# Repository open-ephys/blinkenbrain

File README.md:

# Blinkenbrain
A mouse brain pendant with chaotic tendencies. It implements a variant of the circuit described in

```
Simple Two-Transistor Single-Supply Resistor–Capacitor Chaotic Oscillator
Lars Keuninckx, Guy Van der Sande, and Jan Danckaert
IEEE TRANSACTIONS ON CIRCUITS AND SYSTEMS—II: EXPRESS BRIEFS, VOL. 62, NO. 9, SEPTEMBER 2015
```

and uses its strange dynamics to blink a blinkenlight.

## How does it blink?

The circuit consists of a RC phase shift oscillator (blue) combined with what amounts to a tunable Schmitt trigger (red).
The position of the trimpot (RV1) determines if the effect of the Schmitt trigger on the oscillator.

- When the wiper of RV1 is tuned to 0Ω, Q1B does not conduct, and the Schmitt trigger is effectively removed from the circuit
- When the wiper of RV1 is tuned to 100kΩ, Q1B acts as trigger without hysteresis, and therefore conducts in synchrony with the
  RC oscillator.
- When the wiper of RV1 is turned in between these two extremes, a hysteretic path is formed between Q1B's conducting and non-conducting states,
  which results in the emergence of two interacting unstable equilibria and, for some values of RV1, chaotic dynamics.

The gate of an N-channel MOSFET is tied to the collector of Q1A to drive the LED without influencing the
circuit's dynamics. The following image shows V<sub>TP4</sub> vs.V<sub>TP3</sub> when RV1 is tuned to ~70kΩ.

## License
"No Rights Reserved", CC0

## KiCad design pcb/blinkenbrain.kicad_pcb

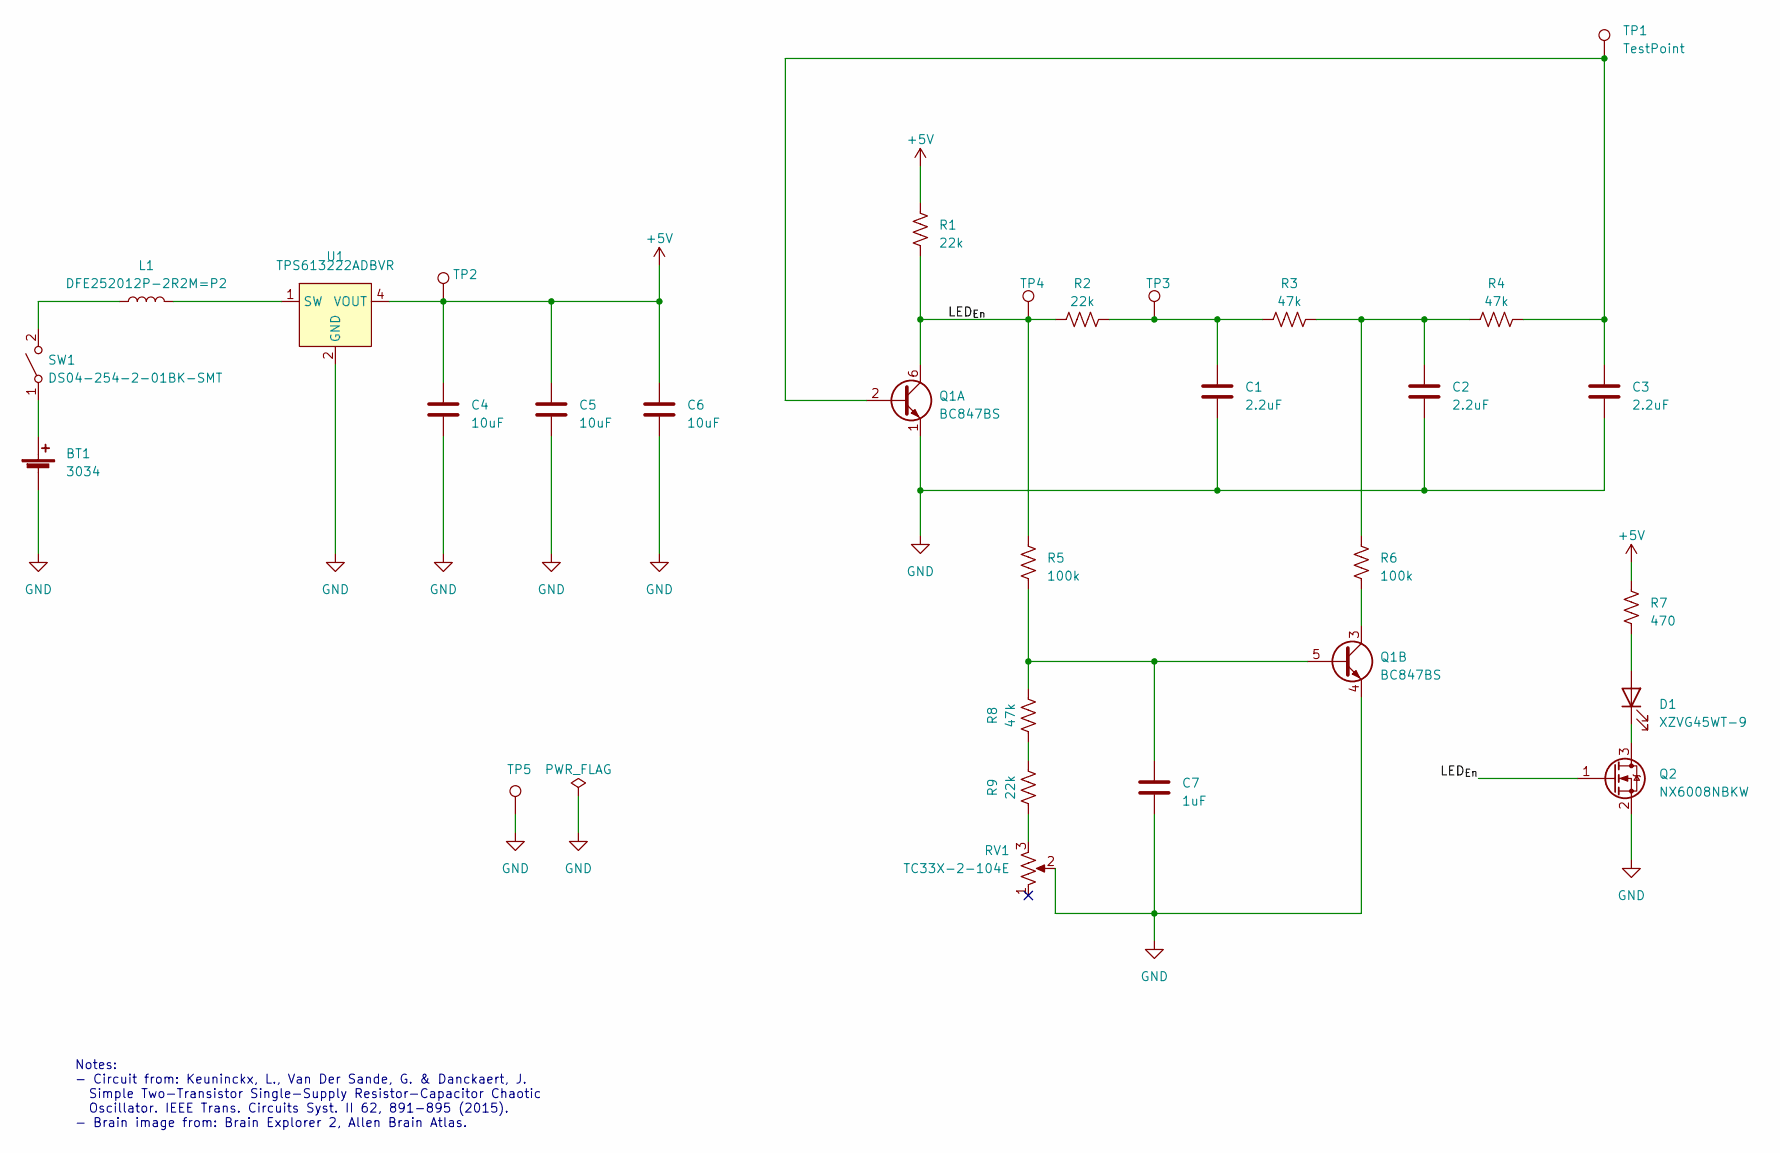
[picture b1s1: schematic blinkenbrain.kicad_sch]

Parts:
BT1: 3034; BatteryHolder_Keystone_3034_1x20mm
C1, C2, C3: 2.2uF; C_0603_1608Metric; Tolerance 5%; Voltage 10V
C4, C5, C6: 10uF; C_0603_1608Metric; Tolerance 20%; Voltage 16V
C7: 1uF; C_0603_1608Metric; Tolerance 5%; Voltage 10V
D1: XZVG45WT-9; SUNLED_PLCC2-INV
L1: DFE252012P-2R2M=P2; L_1008_2520Metric
Q1: BC847BS; SOT-363_SC-70-6
Q2: NX6008NBKW; SOT-23-3
R1, R2, R9: 22k; R_0402_1005Metric; Tolerance 1%
R3, R4, R8: 47k; R_0402_1005Metric; Tolerance 1%
R5, R6: 100k; R_0402_1005Metric; Tolerance 1%
R7: 470; R_0603_1608Metric; Tolerance 1%
RV1: TC33X-2-104E; BOURNS_TC33
SW1: DS04-254-2-01BK-SMT; SW_DIP_SPSTx01_Slide_6.7x4.1mm_W8.61mm_P2.54mm_LowProfile
TP1, TP2, TP3, TP4, TP5: TestPoint; TestPoint_Pad_D2.0mm
U1: TPS613222ADBVR; SOT-23-5

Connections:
+5V: C4.1, C5.1, C6.1, R1.1, R7.2, TP2.1, U1.4 (VOUT)
/LED_{En}: Q1.6 (C1), Q2.1 (G), R1.2, R2.1, R5.2, TP4.1
GND: BT1.2 (-), C1.2, C2.2, C3.2, C4.2, C5.2, C6.2, C7.2, Q1.1 (E1), Q1.4 (E2), Q2.2 (S), RV1.2, TP5.1, U1.2 (GND)
unnamed: BT1.1 (+), SW1.1 (A)
unnamed: C1.1, R2.2, R3.1, TP3.1
unnamed: C2.1, R3.2, R4.1, R6.2
unnamed: D1.2 (A), R7.1
unnamed: D1.1 (K), Q2.3 (D)
unnamed: C3.1, Q1.2 (B1), R4.2, TP1.1
unnamed: C7.1, Q1.5 (B2), R5.1, R8.2
unnamed: Q1.3 (C2), R6.1
unnamed: R8.1, R9.2
unnamed: R9.1, RV1.3
unnamed: L1.1, SW1.2 (B)
unnamed: L1.2, U1.1 (SW)

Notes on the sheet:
Notes: - Circuit from: Keuninckx, L., Van Der Sande, G. & Danckaert, J. Simple Two-Transistor Single-Supply Resistor-Capacitor Chaotic Oscillator. IEEE Trans. Circuits Syst. II 62, 891-895 (2015). - Brain image from: Brain Explorer 2, Allen Brain Atlas.

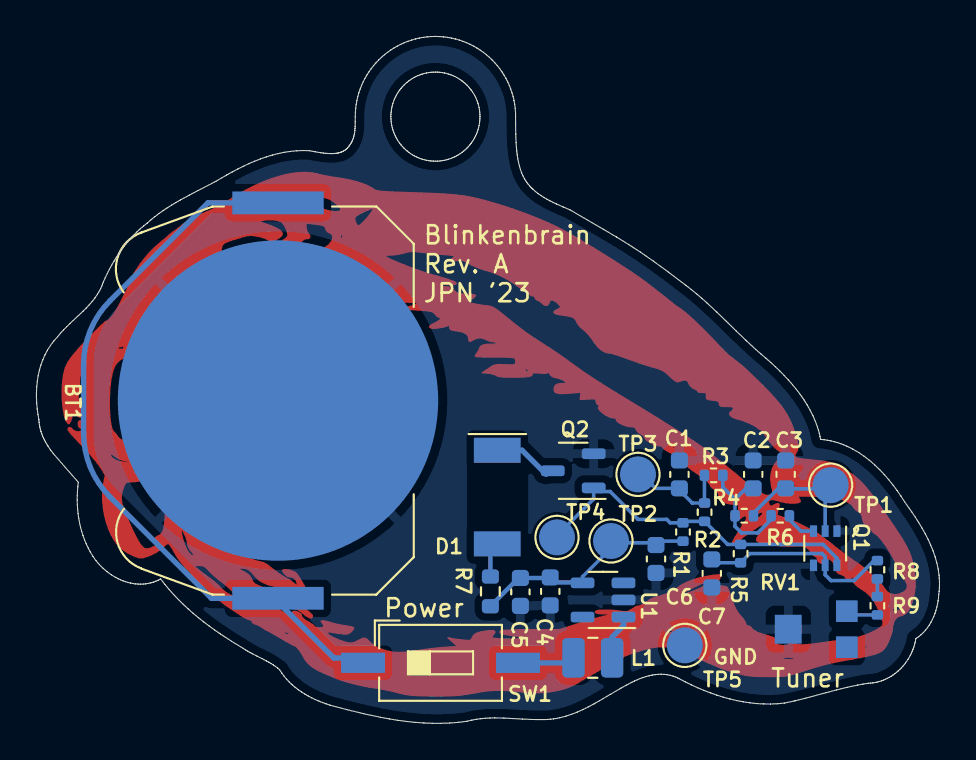
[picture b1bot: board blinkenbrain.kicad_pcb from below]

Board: 2 copper layers, 50.2 x 38.2 mm, 29 parts (29 on the bottom side), 15 nets.

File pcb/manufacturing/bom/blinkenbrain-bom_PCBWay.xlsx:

|  |  | Blinkenbrain 1 PCS BOM
Item # | *Designator | *Qty | Manufacturer | *Mfg Part # | Description / Value | *Package/Footprint | Type | Your Instructions / Notes
1 | U1 | 1 | Texas Instruments | TPS613222ADBVR | IC REG BOOST 5V 2.5A SOT23-5 | SOT23-5 | SMD
2 | SW1 | 1 | Dealon | SC-01KP | DIP switch, 1-bit | 0.1" DIP | SMD
3 | RV1 | 1 | Bourns | TC33X-2-104E | TRIMMER 100K OHM 0.1W J LEAD TOP | TC33 | SMD
4 | R1, R2, R9 | 3 | Walsin | WR04X2202FTL | RES 22K OHM 1/16W 1% 0402 SMD | 0402 | SMD
5 | R3, R4, R8 | 3 | YAGEO | RC0402FR-1347KL | RES 47K OHM 1/16W 1% 0402 SMD | 0402 | SMD
6 | R5, R6 | 2 | Walsin | WR04X1003FTL | RES 100K OHM 1/16W 1% 0402 SMD | 0402 | SMD
7 | R7 | 1 | Rohm | ESR03EZPF4700 | RES 470 OHM 1/4W 1% 0603 SMD | 0603 | SMD
8 | Q1 | 1 | Diodes Inc | BC847BS-7-F | TRANS 2NPN 45V 0.1A SOT363 | SOT363 | SMD
9 | Q2 | 1 | Nexperia | NX6008NBKWX | N-Channel 60 V 250mA (Ta) 270mW (Ta) | SOT323/SC-70 | SMD
10 | L1 | 1 | Murata | DFE252012P-2R2M=P2 | FIXED IND 2.2UH 2.2A 0.084OHM SM | 1008 | SMD
11 | D1 | 1 | SunLED | XZVG45WT-9 | LED GREEN CLEAR 2PLCC SMD | 2PLCC Inverted | SMD
12 | C1, C2, C3 | 3 | Samsung | CL10B225KP8NNNC | Ceramic Cap 2.2uF X7R 5% 10V | 0603 | SMD | X5R is acceptable
13 | C4, C5, C6 | 3 | Murata | GRM188R61E106KA73J | Ceramic Cap 10uF X5R 20% 25V | 0603 | SMD | Can go down to 16V
14 | C7 | 1 | KYOCERA | KGM15CR71C105JT | Ceramic Cap 1uF X7R 5% 16V | 0603 | SMD | X5R is acceptable
15 | BT1 | 1 | Keystone | 3034 | BATT RETAINER COIN 20MM 1CEL SMD | 3034 | SMD
Need a quick and accurante quote? Need an efficient production? Please read SMT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
Click for Instructions on How to Create a BOM
 |  |  |  |  |  |  | open-ephys:DEALON_DIP_SPSTx01_SC-01KP_W7.62mm_P1.27mm | ~ |  |  |  | 1

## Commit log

2023-09-21 Add more accurate spice models of circuit
    - Use models for the exact part numbers the parts called for on the BOM
2023-09-21 Added assuembly documents for jlcpcb
2023-10-04 Rev. B
    - Small changes after testing (completely functional but some foot
    prints were a bit off)
    - Changed DIP switch so that its easier to actuate
    - Created 20 peice panel
2023-10-06 Forgot to add panel.
2023-10-12 Improve README
    - Add a description of how the circuit works
2023-10-12 Update README.md
    - Resize schematic
2023-10-12 Added scope XY plots.
2023-11-08 Added pamphlet
    - For SfN 2023
2023-11-16 Add social media post materials.
2024-09-10 Rev. C
    - Fix minor silkscreen errors
    - Remove extra supports from one PCB in center of panel
2025-09-23 Initial revision D
    - Parts optimized for JLCPCB production
    - Awaiting on some digikey sourced parts to reach their warehouse. I
    will then use these design files and either merge or update if changes
    are needed.
2026-03-17 Remove outer mouse bites to aid depanelization
    - The outer mouse bites made it easy for the tabs to stay with the
    brains when they were removed
    - Update spice model to accurately reflect LED current limit resistor.
